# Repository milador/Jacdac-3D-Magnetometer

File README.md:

# Jacdac-3D-Magnetometer
A <a href="https://microsoft.github.io/jacdac-docs/">Jacdac</a> 3D-Magnetometer Module based on <a href="https://www.infineon.com/cms/en/product/sensor/magnetic-sensors/magnetic-position-sensors/3d-magnetics/tlv493d-a1b6/">TLV493D</a> 3-axis magnetometer sensor.

## Top View: 

## Bottom View:

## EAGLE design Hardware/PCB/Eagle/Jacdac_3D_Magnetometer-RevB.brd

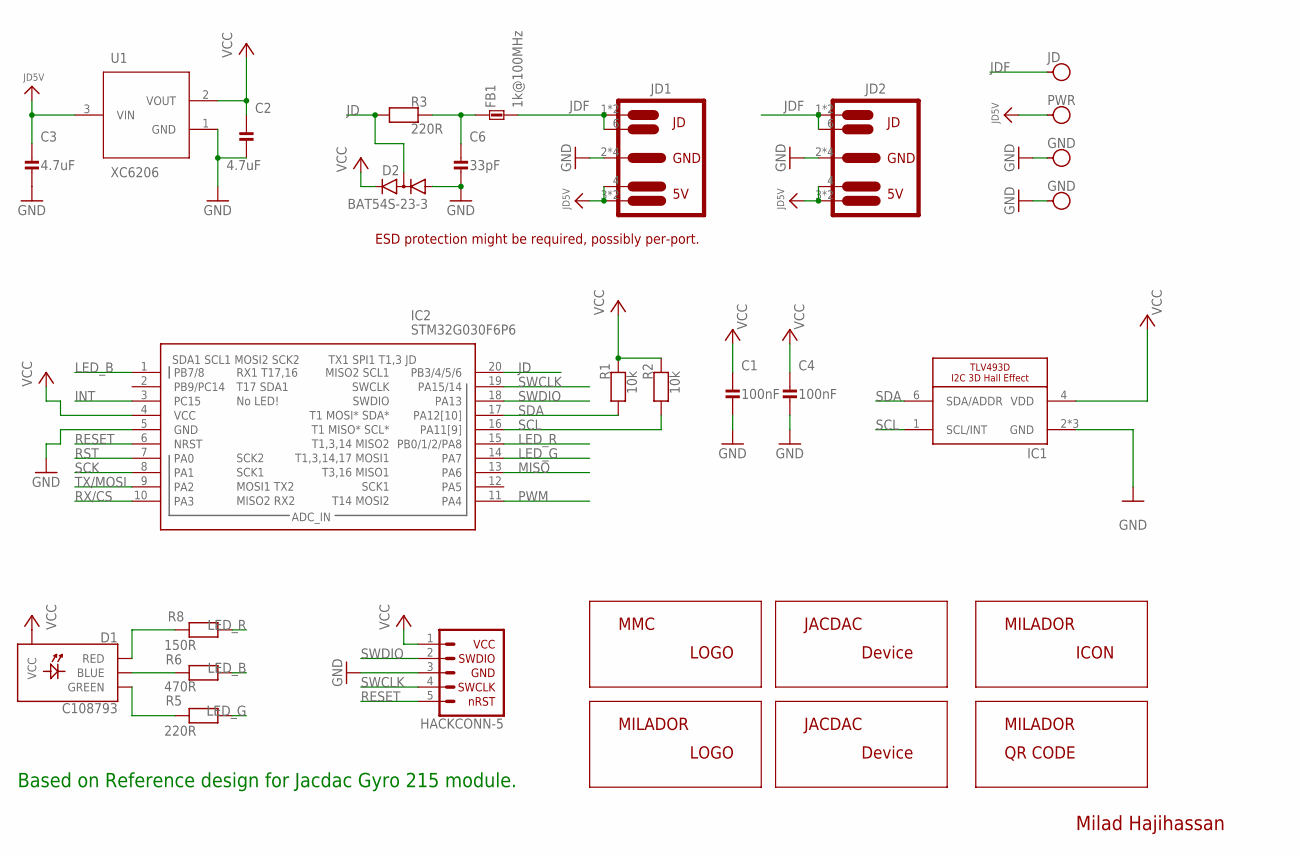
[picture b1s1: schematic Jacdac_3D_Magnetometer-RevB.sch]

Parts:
C1, C4: 100nF; 0402
C2, C3: 4.7uF; 0402
C6: 33pF; 0402
D1: C108793; LED-RGB-2121
D2: BAT54S-23-3; SOT23-3
FB1: 1k@100MHz; 0402
IC1: TLV493D; SOT23-6
IC2: STM32G030F6P6; SOP65P640X120-20N
J1: JD; M3-HOLE-DATA
J2: PWR; M3-HOLE-PWR
J3, J4: GND; M3-HOLE-GND
J5: HACK-CONNECT-5; HC5-22-62
JD1, JD2: JACDAC-EDGE-OUTIE; JD-EDGE-OUTIE
LABEL_DEVICE: MILADOR-JACDAC-DEVICE-MAGNETOMETER; JACDAC-3D-MAGNETOMETER
LABEL_ICON: MILADOR-ICON-MAG; MILADOR_ICON_MAGNETOMETER
LABEL_LOGO1: MILADOR-LOGO-SM; MILADOR_LOGO2
LABEL_LOGO2: MMC_LOGO-XSM; MMC_X-SMALL_LOGO
LABEL_QRCODE: MILADOR-QR-CODE-JACDAC-MAGNETOMETER; MILADOR_QR_JACDAC_MAGNETOMETER
LABEL_TLV493D: MILADOR-JACDAC-DEVICE-TLV493D; JACDAC-TLV493D
R1, R2: 10k; 0402
R3, R5: 220R; 0402
R6: 470R; 0402
R8: 150R; 0402
U1: XC6206; SOT23-3-W

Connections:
GND: C1.2, C2.2, C3.2, C4.2, C6.2, D2.1 (A1), IC1.2 (GND), IC1.3 (GND), IC1.5 (GND), IC2.5 (GND), J3.H, J4.H, J5.3 (GND), JD1.2 (1), JD1.5 (1), JD1.P$2 (1), JD1.P$4 (1), JD2.2 (1), JD2.5 (1), JD2.P$2 (1), JD2.P$4 (1), U1.1 (GND)
INT: IC2.3 (PC15)
JD: D2.3 (C1A2), IC2.20 (PB3/4/5/6), R3.1
JD5V: C3.1, J2.H, JD1.3, JD1.4, JD1.P$1 (3), JD2.3, JD2.4, JD2.P$1 (3), U1.3 (VIN)
JDF: FB1.2, J1.H, JD1.1 (2), JD1.6, JD1.P$3 (2), JD2.1 (2), JD2.6, JD2.P$3 (2)
LED_B: IC2.1 (PB7/8), R6.1
LED_G: IC2.14 (PA7), R5.1
LED_R: IC2.15 (PB0/1/2/PA8), R8.1
MISO: IC2.13 (PA6)
unnamed: C6.1, FB1.1, R3.2
unnamed: D1.B- (BLUE), R6.2
unnamed: D1.R- (RED), R8.2
unnamed: D1.G- (GREEN), R5.2
PWM: IC2.11 (PA4)
RESET: IC2.6 (NRST), J5.5 (NRST)
RST: IC2.7 (PA0)
RX/CS: IC2.10 (PA3)
SCK: IC2.8 (PA1)
SCL: IC1.1 (SCL/INT), IC2.16 (PA11[9]), R2.1
SDA: IC1.6 (SDA/ADDR), IC2.17 (PA12[10]), R1.1
SWCLK: IC2.19 (PA15/14), J5.4 (SWCLK)
SWDIO: IC2.18 (PA13), J5.2 (SWDIO)
TX/MOSI: IC2.9 (PA2)
VCC: C1.1, C2.1, C4.1, D1.PLUS (VCC), D2.2 (C2), IC1.4 (VDD), IC2.4 (VCC), J5.1 (VCC), R1.2, R2.2, U1.2 (VOUT)

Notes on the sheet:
Based on Reference design for Jacdac Gyro 215 module.
ESD protection might be required, possibly per-port.
Milad Hajihassan

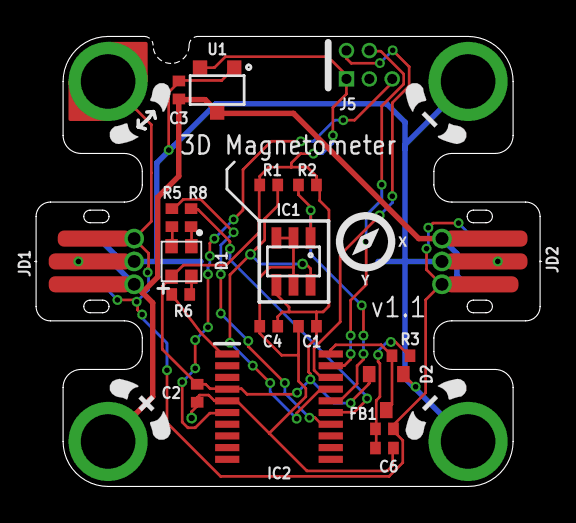
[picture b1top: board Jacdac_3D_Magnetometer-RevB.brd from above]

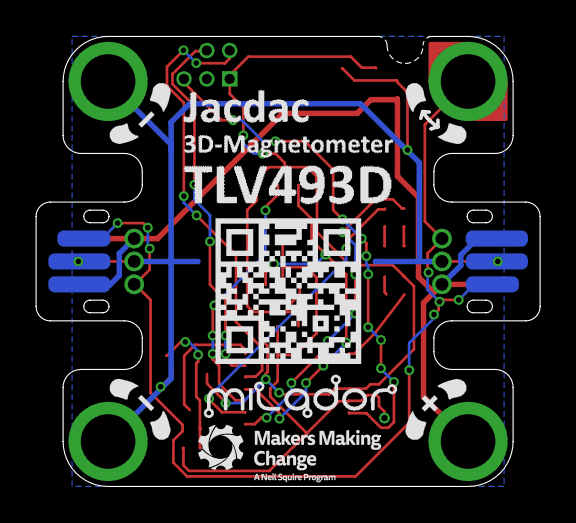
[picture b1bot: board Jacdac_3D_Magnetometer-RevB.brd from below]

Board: 2 copper layers, 28.0 x 25.0 mm, 30 parts (5 on the bottom side), 17 nets.

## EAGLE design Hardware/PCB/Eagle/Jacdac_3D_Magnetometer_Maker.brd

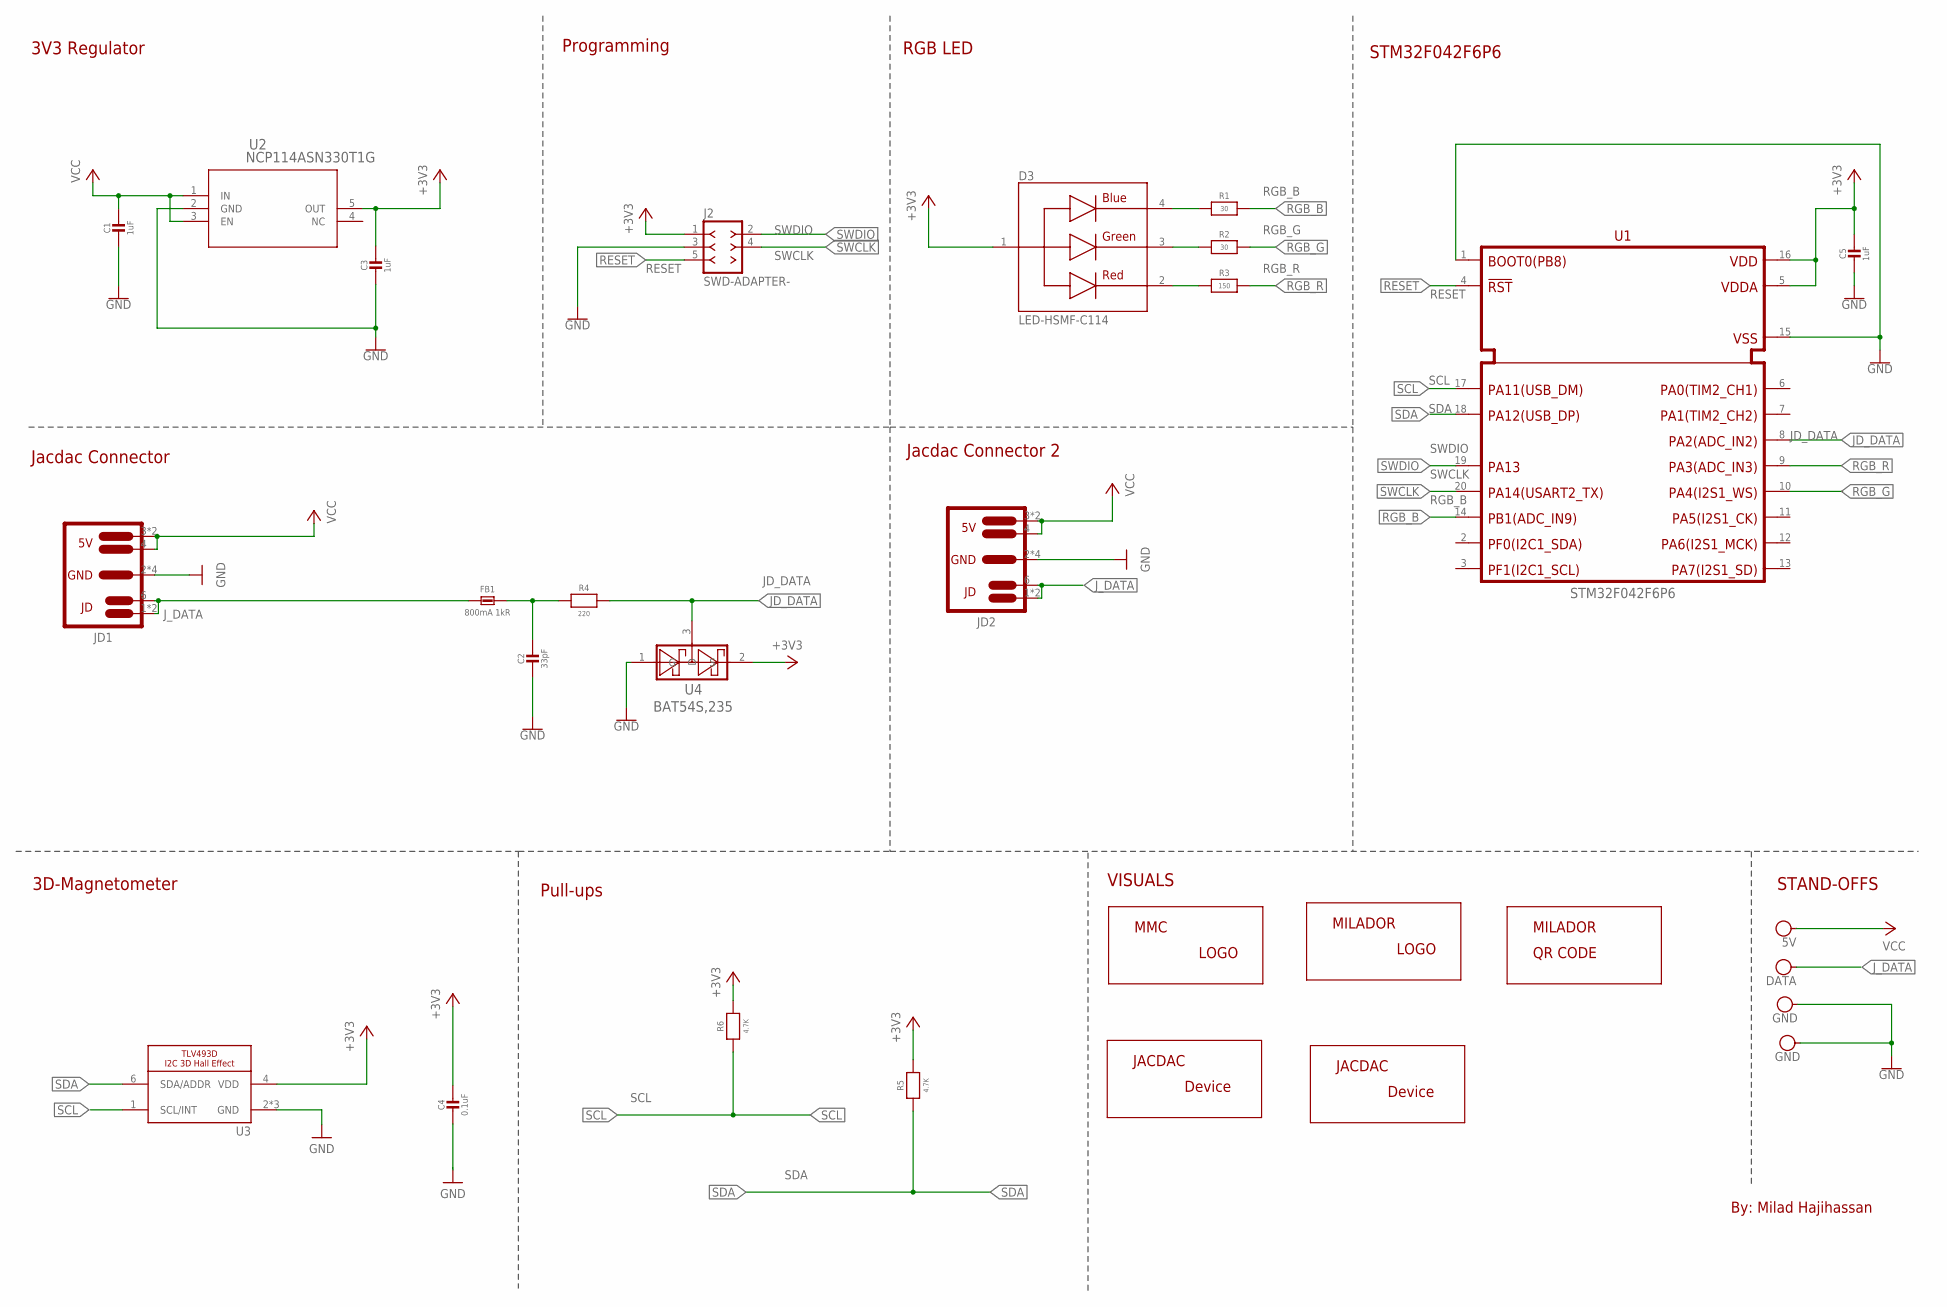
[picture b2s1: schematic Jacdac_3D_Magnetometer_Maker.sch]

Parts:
C1, C3: 1uF; 0603-NO
C2: 33pF; 0603
C4: 0.1uF; 0603-NO
C5: 1uF; 0603
D3: LED-HSMF-C114; DIOSC160X150X35-4N
FB1: 800mA 1kR; 0603-NO
J2: SWD-ADAPTER-; SWD-ADAPTER
J3: 5V; M3-HOLE-PWR-OUTL
J4: DATA; M3-HOLE-DATA-NOTCH
J5, J6: GND; M3-HOLE-GND
JD1, JD2: JACDAC-EDGE-OUTIE; JD-EDGE-OUTIE
LABEL_JACDAC_PS: MILADOR-JACDAC-DEVICE-MAGNETOMETER; JACDAC-3D-MAGNETOMETER
LABEL_MILADOR: MILADOR-LOGO-; MILADOR_LOGO1
LABEL_QR_CODE: MILADOR-QR-CODE-JACDAC-MAGNETOMETER; MILADOR_QR_JACDAC_MAGNETOMETER
LABEL_TLV493D: MILADOR-JACDAC-DEVICE-TLV493D; JACDAC-TLV493D
MMC_LOGO: MMC_LOGO-XSM; MMC_X-SMALL_LOGO
R1, R2: 30; 0603
R3: 150; 0603
R4: 220; 0603
R5, R6: 4.7K; 0603
U1: STM32F042F6P6; TSSOP20
U2: NCP114ASN330T1G; TSOP-5_ONS
U3: TLV493D; SOT23-6
U4: BAT54S,235; SOT23-3

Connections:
+3V3: C3.1, C4.1, C5.1, D3.1, J2.1 (VCC_1), R5.2, R6.2, U1.5 (VDDA), U1.16 (VDD), U2.5 (OUT), U3.4 (VDD), U4.2 (S)
GND: C1.2, C2.2, C3.2, C4.2, C5.2, J2.3 (GND_3), J5.H, J6.H, JD1.2 (1), JD1.5 (1), JD1.P$2 (1), JD1.P$4 (1), JD2.2 (1), JD2.5 (1), JD2.P$2 (1), JD2.P$4 (1), U1.1 (BOOT0), U1.15 (VSS), U2.2 (GND), U3.2 (GND), U3.3 (GND), U3.5 (GND), U4.1 (G)
JD_DATA: R4.2, U1.8 (PA2), U4.3 (D)
J_DATA: FB1.2, J4.H, JD1.1 (2), JD1.6, JD1.P$3 (2), JD2.1 (2), JD2.6, JD2.P$3 (2)
unnamed: D3.4, R1.1
unnamed: D3.3, R2.1
unnamed: D3.2, R3.1
unnamed: C2.1, FB1.1, R4.1
RESET: J2.5 (RESET_5), U1.4 (!RST)
RGB_B: R1.2, U1.14 (PB1)
RGB_G: R2.2, U1.10 (PA4)
RGB_R: R3.2, U1.9 (PA3)
SCL: R6.1, U1.17 (PA11), U3.1 (SCL/INT)
SDA: R5.1, U1.18 (PA12), U3.6 (SDA/ADDR)
SWCLK: J2.4 (SWCLK_4), U1.20 (PA14)
SWDIO: J2.2 (SWDIO_2), U1.19 (PA13)
VCC: C1.1, J3.H, JD1.3, JD1.4, JD1.P$1 (3), JD2.3, JD2.4, JD2.P$1 (3), U2.1 (IN), U2.3 (EN)

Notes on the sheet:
By: Milad Hajihassan
STAND-OFFS
VISUALS
Programming
3V3 Regulator
RGB LED
Jacdac Connector
3D-Magnetometer
Pull-ups
Jacdac Connector 2
STM32F042F6P6

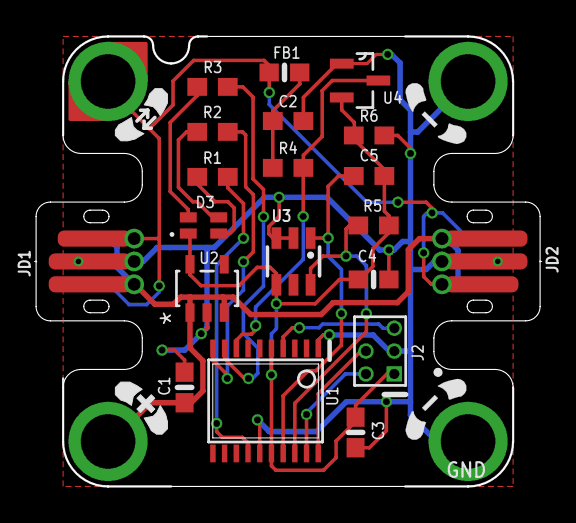
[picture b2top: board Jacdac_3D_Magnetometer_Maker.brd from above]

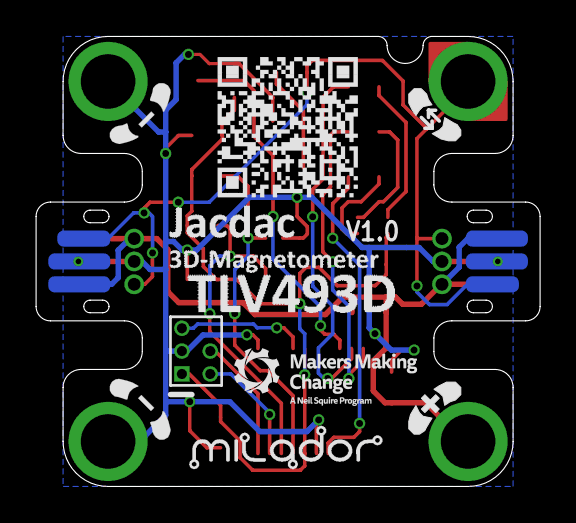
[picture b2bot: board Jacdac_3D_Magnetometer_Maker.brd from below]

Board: 2 copper layers, 28.0 x 25.0 mm, 29 parts (5 on the bottom side), 17 nets.

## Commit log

2022-07-06 Added version 1.0 design files
2022-07-07 Added RevB
2022-07-08 Updated BOM
2022-07-09 Updated RevB
2022-07-13 Updated RevB design to match pinouts of other Jacdac modules
2022-07-14 Updated board.pdf
2022-07-14 updated images
2022-07-14 Updated components value
2022-07-16 Updated Magnetometer icon
2022-08-10 Updated BOM for SMT

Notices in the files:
parts and their libraries:
COPYRIGHT: Copyright (C) 2021 Ultra Librarian. All rights reserved.
SparkFun-PowerSymbols: Licensing: Creative Commons ShareAlike 4.0 International - https://creativecommons.org/licenses/by-sa/4.0
